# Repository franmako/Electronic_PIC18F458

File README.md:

# Electronic_PIC18F458
This an electronics group project from my second year in University. 

The project is about interfacing an LM35 temperature reading module with a microcontroller(PIC 18F458).

We had to do the whole project from scratch:
  - Designing the circuit schematics with Proteus
  - Designing the board schematics with Eagle
  - Writing the CCS code to read the temperature and display it with seven segment displays
  - Writing a Java code to choose an alert temperature from a PC connected to the PIC with a Serial connector.
  - Managing and sending the data to and from the PIC - PC 
  - Display alert on PC with the Java interface if temperature is higher than the limit set

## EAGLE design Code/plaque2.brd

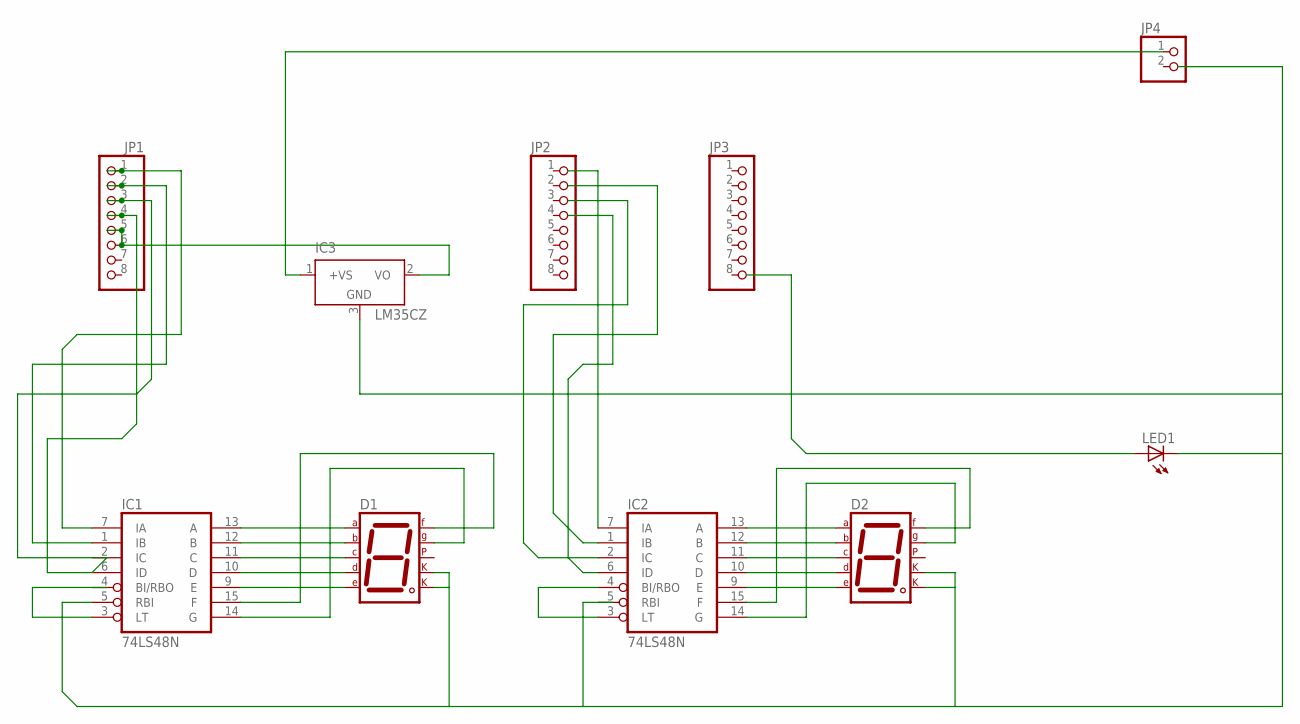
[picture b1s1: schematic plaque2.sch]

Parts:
D1, D2: 7SEG-CK; 7SEG-13
IC1, IC2: 74LS48N; DIL16
IC3: LM35CZ; TO92
JP1, JP2, JP3: PINHD-1X8; 1X08
JP4: PINHD-1X2; 1X02
LED1: LED_E; LED_1206

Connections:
GND: IC1.8 (GND), IC2.8 (GND)
unnamed: D1.7 (A), IC1.13 (A)
unnamed: D1.6 (B), IC1.12 (B)
unnamed: D1.4 (C), IC1.11 (C)
unnamed: D1.2 (D), IC1.10 (D)
unnamed: D1.1 (E), IC1.9 (E)
unnamed: D1.9 (F), IC1.15 (F)
unnamed: D1.10 (G), IC1.14 (G)
unnamed: D2.7 (A), IC2.13 (A)
unnamed: D2.6 (B), IC2.12 (B)
unnamed: D2.4 (C), IC2.11 (C)
unnamed: D2.2 (D), IC2.10 (D)
unnamed: D2.1 (E), IC2.9 (E)
unnamed: D2.9 (F), IC2.15 (F)
unnamed: D2.10 (G), IC2.14 (G)
unnamed: D1.3 (CK1), D1.8 (CK2), D2.3 (CK1), D2.8 (CK2), IC1.5 (RBI), IC3.3 (GND), LED1.C
unnamed: IC1.3 (LT), IC1.4 (BI/RBO)
unnamed: IC2.3 (LT), IC2.4 (BI/RBO)
unnamed: IC1.7 (IA), JP1.1
unnamed: IC1.1 (IB), JP1.2
unnamed: IC1.6 (ID), JP1.3, JP1.4
unnamed: IC3.2 (VO), JP1.5, JP1.6
unnamed: IC3.1 (+VS), JP4.1
VCC: IC1.16 (VCC), IC2.16 (VCC)

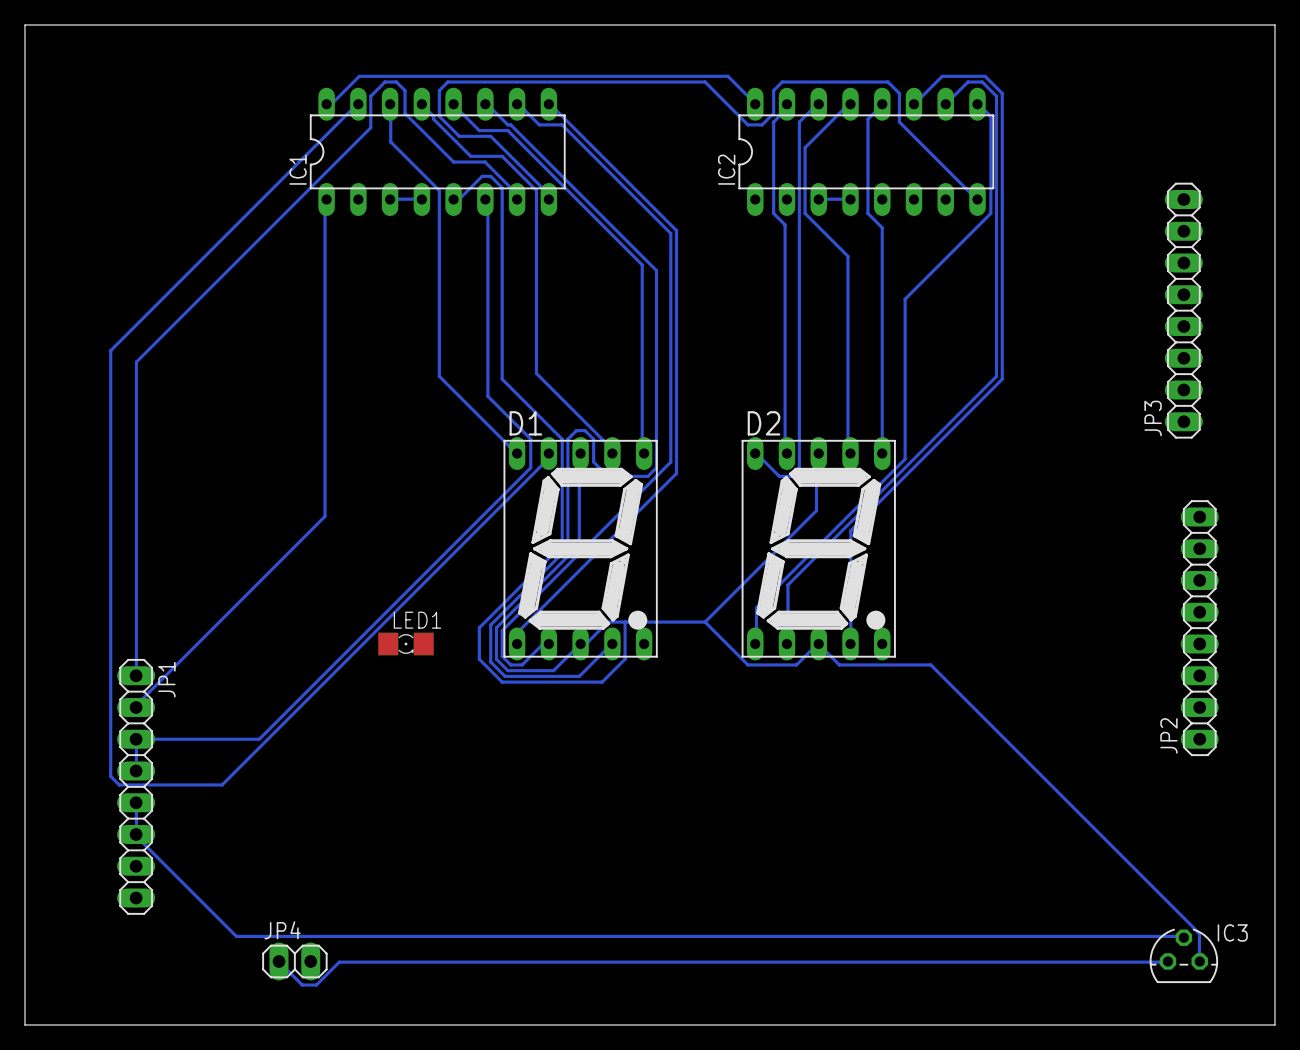
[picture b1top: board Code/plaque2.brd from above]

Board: 2 copper layers, 100.0 x 80.0 mm, 10 parts (0 on the bottom side), 24 nets.

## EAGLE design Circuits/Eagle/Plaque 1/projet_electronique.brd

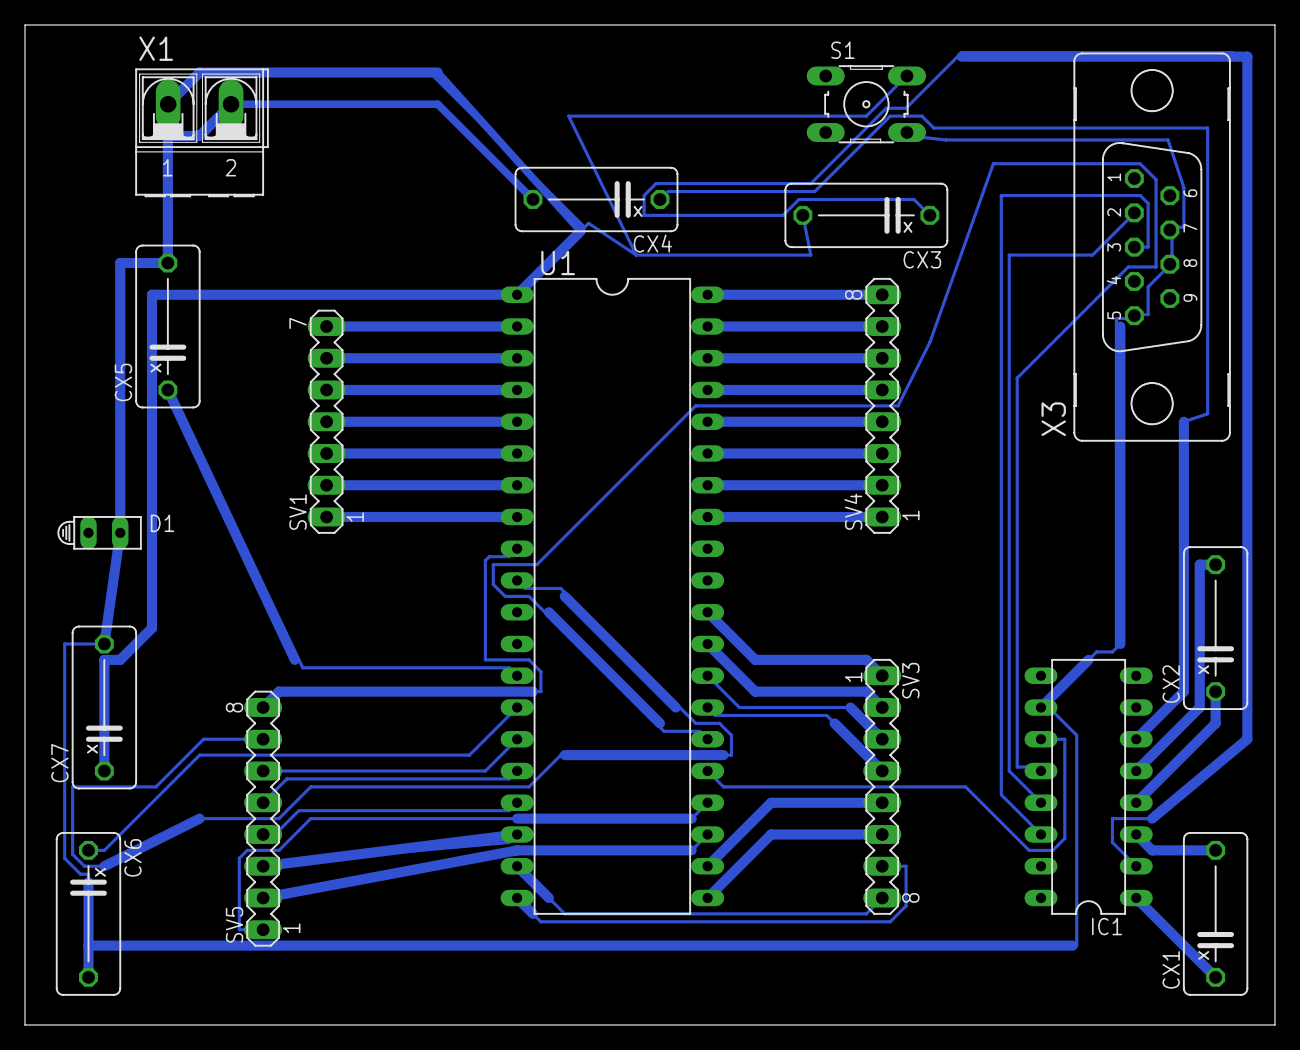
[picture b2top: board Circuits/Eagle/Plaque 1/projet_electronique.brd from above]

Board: 2 copper layers, 100.0 x 80.0 mm, 17 parts (0 on the bottom side), 45 nets.

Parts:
CX1, CX2, CX3, CX4: 1u; XC10B5
CX5, CX6: 15p; XC10B5
CX7: 680n; XC10B5
D1: HLMP6
IC1: MAX232; DIL16
S1: B3F-10XX
SV1: MA07-1
SV3, SV4, SV5: MA08-1
U1: PIC16F877P; DIL40
X1: AK500/2-H
X3: F09V

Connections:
unnamed: CX4.2, CX5.2, CX6.2, CX7.2, D1.K, IC1.10, S1.4, X1.2, X3.5, X3.7, X3.8
unnamed: CX5.1, U1.13
unnamed: CX1.1, IC1.1
unnamed: CX3.2, CX7.1, S1.2, U1.1, X1.1
unnamed: CX6.1, U1.14
unnamed: CX1.2, IC1.3
unnamed: CX2.1, IC1.4
unnamed: CX2.2, IC1.5
unnamed: CX3.1, IC1.2
unnamed: CX4.1, IC1.6
unnamed: IC1.11, U1.25
unnamed: IC1.12, U1.26
unnamed: SV1.7, U1.2
unnamed: IC1.14, X3.3
unnamed: IC1.13, X3.2
unnamed: SV4.1, U1.33
unnamed: SV4.2, U1.34
unnamed: SV4.3, U1.35
unnamed: SV4.4, U1.36
unnamed: SV1.6, U1.3
unnamed: SV1.5, U1.4
unnamed: SV1.4, U1.5
unnamed: SV1.3, U1.6
unnamed: SV1.2, U1.7
unnamed: SV1.1, U1.8
unnamed: SV3.8, U1.19
unnamed: SV3.7, U1.20
unnamed: SV3.6, U1.21
unnamed: SV3.5, U1.22
unnamed: SV3.4, U1.27
unnamed: SV3.3, U1.28
unnamed: SV3.2, U1.29
unnamed: SV3.1, U1.30
unnamed: SV4.5, U1.37
unnamed: SV4.6, U1.38
unnamed: SV4.7, U1.39
unnamed: SV4.8, U1.40
unnamed: SV5.8, U1.9
unnamed: SV5.7, U1.10
unnamed: SV5.6, U1.15
unnamed: SV5.5, U1.16
unnamed: SV5.4, U1.17
unnamed: SV5.3, U1.18
unnamed: SV5.2, U1.23
unnamed: SV5.1, U1.24

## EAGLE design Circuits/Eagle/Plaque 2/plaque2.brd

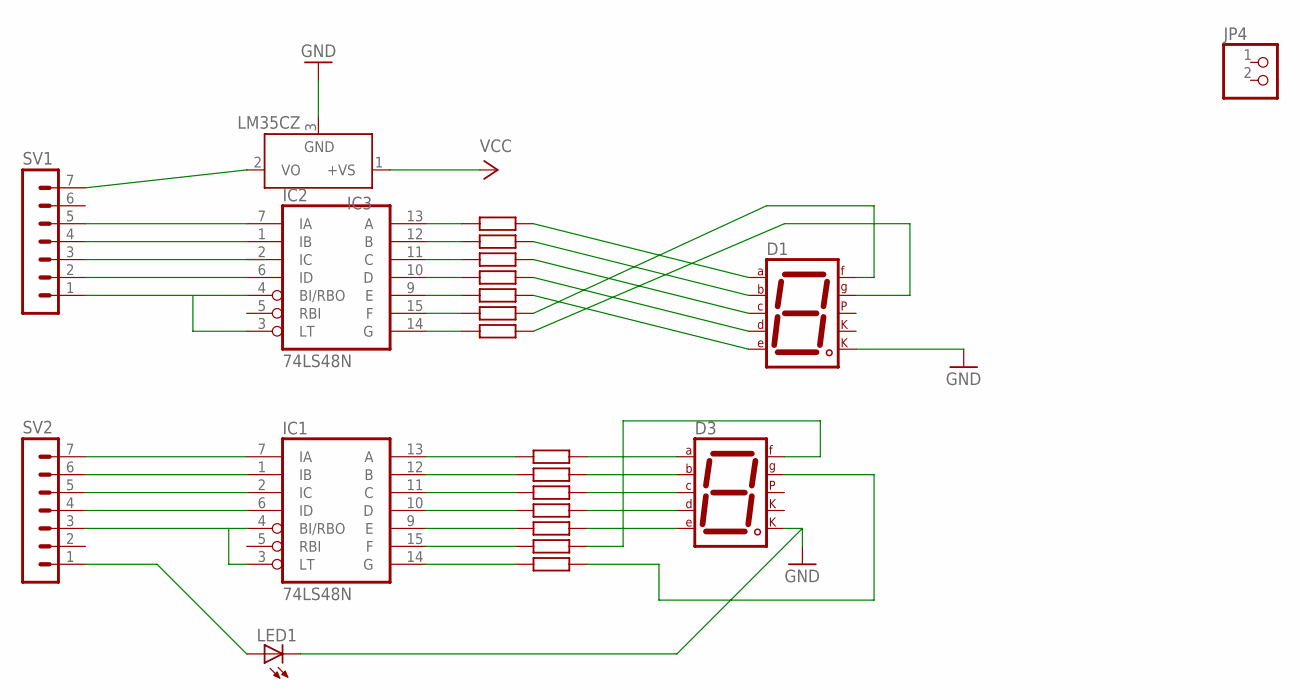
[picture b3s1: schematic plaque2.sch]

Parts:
D1, D3: 7SEG-CK; 7SEG-13
IC1, IC2: 74LS48N; DIL16
IC3: LM35CZ; TO92
JP4: PINHD-1X2; 1X02
LED1: LED_E; LED_1206
SV1, SV2: MA07-1

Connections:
GND: D1.8 (CK2), D3.8 (CK2), IC1.8 (GND), IC2.8 (GND), IC3.3 (GND), LED1.C
unnamed: IC3.2 (VO), SV1.7
unnamed: IC2.7 (IA), SV1.5
unnamed: IC2.1 (IB), SV1.4
unnamed: IC2.6 (ID), SV1.2
unnamed: IC2.3 (LT), IC2.4 (BI/RBO), SV1.1
unnamed: IC1.7 (IA), SV2.7
unnamed: IC1.1 (IB), SV2.6
unnamed: IC1.2 (IC), SV2.5
unnamed: IC1.6 (ID), SV2.4
unnamed: IC1.3 (LT), IC1.4 (BI/RBO), SV2.3
unnamed: LED1.A, SV2.1
VCC: IC1.16 (VCC), IC2.16 (VCC), IC3.1 (+VS)

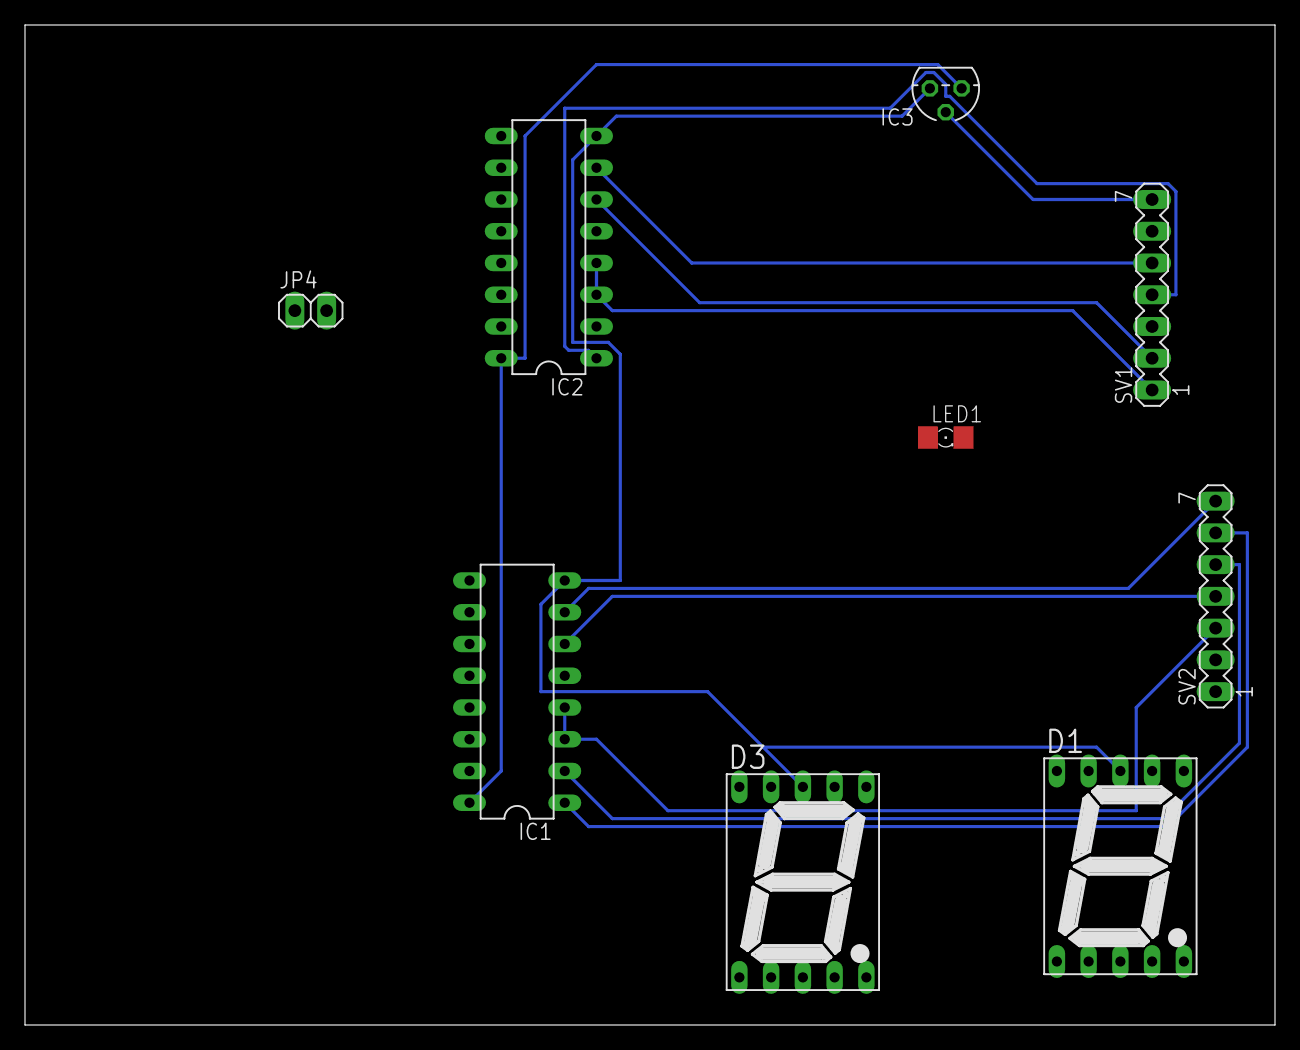
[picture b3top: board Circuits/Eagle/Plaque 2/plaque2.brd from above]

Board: 2 copper layers, 100.0 x 80.0 mm, 9 parts (0 on the bottom side), 13 nets.

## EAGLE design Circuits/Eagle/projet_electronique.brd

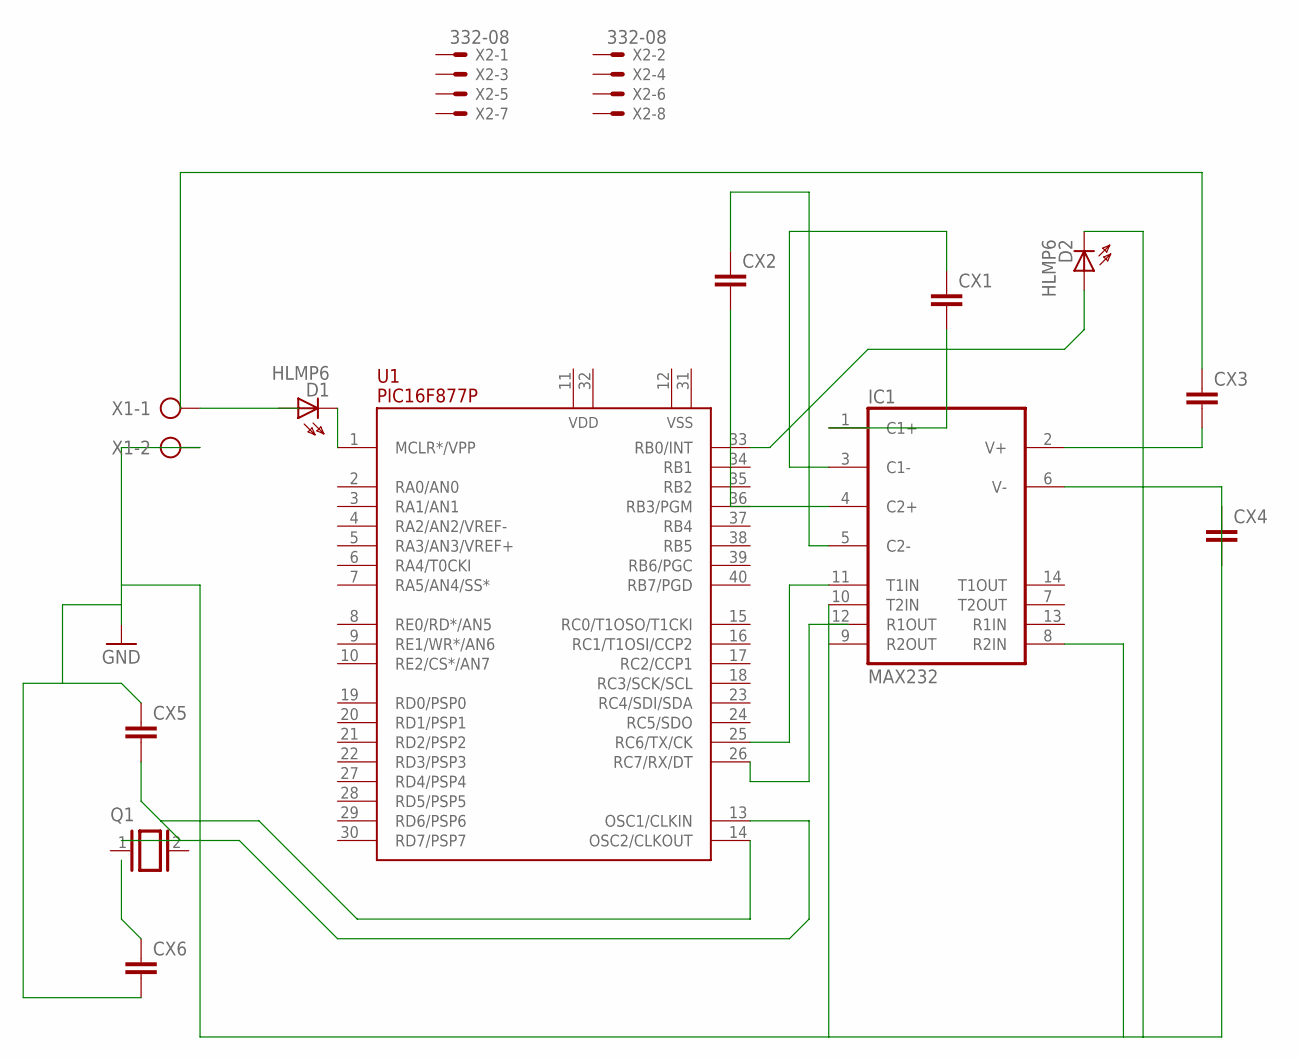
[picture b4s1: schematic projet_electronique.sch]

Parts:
CX1, CX2, CX3, CX4, CX5, CX6: CXXC10B5; XC10B5
D1, D2: HLMP6
IC1: MAX232; DIL16
Q1: XTAL; Q
U1: PIC16F877P; DIL40
X1: AK500/2-H
X2: 332-08

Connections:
GND: CX4.1, CX4.2, CX5.1, CX6.2, D2.K, IC1.6 (V-), IC1.8 (R2IN), IC1.10 (T2IN), IC1.15 (GND), X1.2
unnamed: D1.K, U1.1 (MCLR*/VPP)
unnamed: CX1.2, IC1.1 (C1+)
unnamed: CX1.1, IC1.3 (C1-)
unnamed: CX2.2, IC1.4 (C2+)
unnamed: CX2.1, IC1.5 (C2-)
unnamed: CX3.2, IC1.2 (V+)
unnamed: IC1.11 (T1IN), U1.25 (RC6/TX/CK)
unnamed: D2.A, U1.33 (RB0/INT)
unnamed: CX5.2, U1.13 (OSC1/CLKIN), U1.14 (OSC2/CLKOUT)
VCC: IC1.16 (VCC)

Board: 2 copper layers, 13 parts (0 on the bottom side), 10 nets, no tracks yet.

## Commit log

2015-02-28 Code Arnaud
2015-02-28 Circuit Proteus
2015-02-28 Circuits Eagle + Proteus + Rapport intermédiare word
2015-03-03 Plaque 2 Eagle
2015-03-03 Circuits rapports intermédiares
2015-05-18 Final commit
